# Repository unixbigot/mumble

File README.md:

# Mumble - a very small GRBL

Mumble is a board for [the ESP32 port of GRBL](https://github.com/bdring/Grbl_Esp32), targetted at low-voltage stepper motors. 
It was designed for the Minigraph CNC sticker plotter, but is intended to be usable for other CNC experiments.

It exposes all the GRBL pins, and has three DRV8834 low-votage motor drivers on-board.   
Unlike the more popular A4988, the DRV8834 operates from motor voltage in the range 3v to 10.8v, making it suitable
for low-voltage miniature steppers.

The board also features a lithium battery charge controller.

Change Log,

Issues

Version 1.0 -> 1.3
* Bradley King, fixed double pin 10
* Bradley King, connected enable to vmotor via 47k resistor (datasheet 8.4.3)
* Bradley King, connected charge status led to + v_usb, was floating.

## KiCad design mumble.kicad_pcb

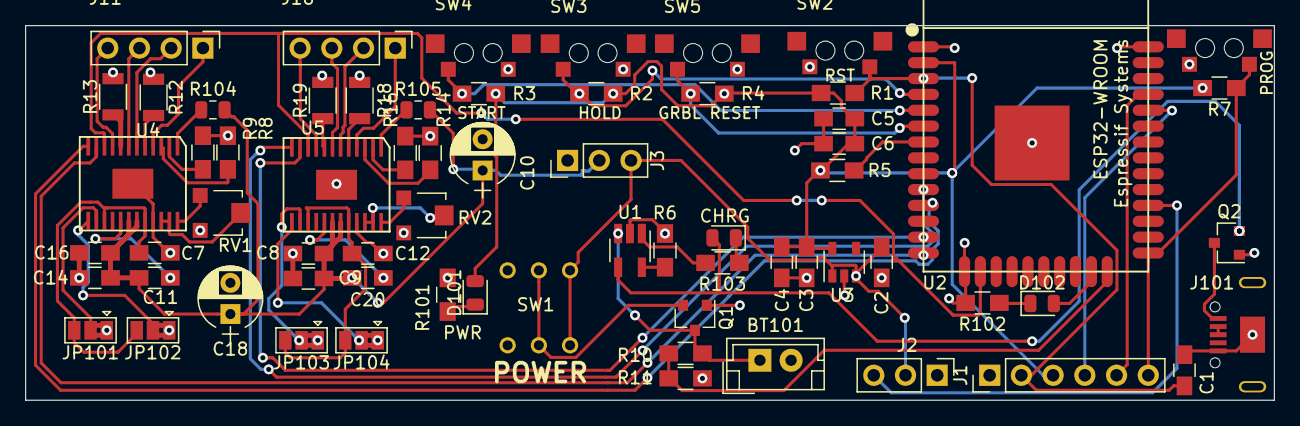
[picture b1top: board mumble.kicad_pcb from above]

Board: 2 copper layers, 100.0 x 30.0 mm, 67 parts (0 on the bottom side), 60 nets.

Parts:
BT101: Battery; JST_EH_B02B-EH-A_02x2.50mm_Straight
C1, C5: 0.1uF; C_0805_HandSoldering
C2, C3: 1uF; C_0805_HandSoldering
C4, C6, C8, C14: 10uF; C_0805_HandSoldering
C7, C12: 4.7uF; C_0805_HandSoldering
C9, C16: 2.2uF; C_0805_HandSoldering
C10, C18: 100uF; CP_Radial_D5.0mm_P2.50mm
C11, C20: 0.01uF; C_0805_HandSoldering
D101, D102: LED; LED_0805_2012Metric
D103: CHRG; LED_0805_2012Metric
J1: Serial; PinHeader_1x06_P2.54mm_Vertical
J2: Servo; Pin_Header_Straight_1x03_Pitch2.54mm
J3: VM sel; Pin_Header_Straight_1x03_Pitch2.54mm
J11: X_MOT; Pin_Header_Straight_1x04_Pitch2.54mm
J16: Z_MOT; Pin_Header_Straight_1x04_Pitch2.54mm
J101: USB_B_Micro; USB_Micro
JP101, JP102, JP103, JP104: Jumper_3_Bridged12; SolderJumper-3_P1.3mm_Bridged2Bar12_Pad1.0x1.5mm
Q1, Q2: IRLML9301; SOT-23
R1, R2, R3, R4, R5, R7, R11: 10k; R_0805_HandSoldering
R6: 1.2K; R_0805_HandSoldering
R8, R9, R14, R16: 47k; R_0805_HandSoldering
R10: 50k; R_0805_HandSoldering
R12, R13, R18, R19: 0.1R; R_1206
R101, R102, R103: 330; R_0805_HandSoldering
R104, R105: 47k; R_0805_2012Metric
RV1, RV2: 10k; Potentiometer_Trimmer-EVM3E
SW1: SW_SPST; CherryPowerSwitch
SW2: Reset; TVBM02
SW3: Hold Button; TVBM02
SW4: Start Button; TVBM02
SW5: Abort Button; TVBM02
SW6: Program; TVBM02
U1: TP4054; SOT-23-5_HandSoldering
U2: ESP32-WROOM
U3: AP2204K-3.3; SOT-23-5
U4, U5: DRV8834; HTSSOP-24

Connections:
+3V3: C3.1, C4.1, C5.1, C6.1, D101.2, J1.3, R1.2, R2.1, R3.1, R4.1, R5.1, R7.2, U2.2, U3.5
+BATT: BT101.1, Q1.3, R10.1, U1.3
/BATT_PROT: D103.2, Q2.2, U1.4
/BATT_SWITCHED: C2.1, J2.2, J3.3, SW1.1, U3.1, U3.3
/BATT_VOLT: R10.2, R11.1, U2.24
/CHRG_ST: R103.2, U1.1
/DOOR: R5.2, U2.7
/GPIO15: D102.2, U2.23
/GRBL_RESET: R4.2, SW5.1, U2.6
/HOLD: R2.2, SW3.1, U2.4
/PROGRAM: J1.6, R7.1, SW6.2, U2.25
/RESET: C1.1, J1.2, R1.1, SW2.2, U2.3
/SERVO: J2.3, U2.28
/START: R3.2, SW4.1, U2.5
/STEP_EN: U2.16, U4.10, U5.10
/UART_RX: J1.4, U2.34
/UART_TX: J1.5, U2.35
/VCP_X: C11.1, U4.17
/VCP_Y: C20.1, U5.17
/VINT_X: C7.1, JP101.3, JP102.3, U4.15, U4.20
/VINT_Y: C12.1, JP103.3, JP104.3, U5.15, U5.20
/VM: C8.1, C9.1, C10.1, C11.2, C14.1, C16.1, C18.1, C20.2, J3.2, R104.2, R105.2, U4.18, U4.19, U5.18, U5.19
/X_DIR: U2.11, U4.12
/X_STEP: U2.14, U4.11
/Y_DIR: U2.10, U5.12
/Y_STEP: U2.13, U5.11
GND: BT101.2, C1.2, C2.2, C3.2, C4.2, C5.2, C6.2, C7.2, C8.2, C9.2, C10.2, C12.2, C14.2, C16.2, C18.2, J1.1, J2.1, J3.1, J101.5, J101.6, JP101.1, JP102.1, JP103.1, JP104.1, Q1.1, Q2.1, R6.2, R8.2, R9.2, R11.2, R12.1, R13.1, R14.2, R16.2, R18.1, R19.1, R101.2, R102.2, RV1.3, RV2.3, SW2.1, SW3.2, SW4.2, SW5.2, SW6.1, U1.2, U2.1, U2.15, U2.38, U2.39, U3.2, U4.21, U4.25, U5.21, U5.25
unnamed: D101.1, R101.1
unnamed: D102.1, R102.1
unnamed: D103.1, R103.1
unnamed: J11.1, U4.4
unnamed: J11.2, U4.6
unnamed: J11.3, U4.7
unnamed: J11.4, U4.9
unnamed: J16.1, U5.4
unnamed: J16.2, U5.6
unnamed: J16.3, U5.7
unnamed: J16.4, U5.9
unnamed: J101.1, Q2.3
unnamed: J101.2, J101.3
unnamed: JP101.2, U4.14
unnamed: JP102.2, U4.13
unnamed: JP103.2, U5.14
unnamed: JP104.2, U5.13
unnamed: Q1.2, SW1.2
unnamed: R6.1, U1.5
unnamed: R8.1, U4.3
unnamed: R9.1, U4.2
unnamed: R12.2, U4.5
unnamed: R13.2, U4.8
unnamed: R14.1, U5.3
unnamed: R16.1, U5.2
unnamed: R18.2, U5.5
unnamed: R19.2, U5.8
unnamed: R104.1, U4.1
unnamed: R105.1, U5.1
unnamed: RV1.1, U4.24
unnamed: RV1.2, U4.22, U4.23
unnamed: RV2.1, U5.24
unnamed: RV2.2, U5.22, U5.23

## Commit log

2018-08-02 Minigraph - a CNC sticker plotter
2018-08-02 Mumble readme
2018-08-02 link to parent project
2018-08-03 Routed PCB
2018-08-03 Updated caps and sense resistors
2018-08-13 Add hardware errata notes
2018-08-17 Updated some of the errata
2018-08-17 Updated errata.md
2018-08-19 Updated power button and USB connector
2018-08-19 Actually saved the PCB this time
2018-08-19 Saved
2018-08-31 Updated to V1.2 of PCB
2018-11-13 added interactive BOM
2018-12-14 version 1.3, fixed nsleep, chrg led not working. change motor pinout for neater routing.
2018-12-14 formatting
